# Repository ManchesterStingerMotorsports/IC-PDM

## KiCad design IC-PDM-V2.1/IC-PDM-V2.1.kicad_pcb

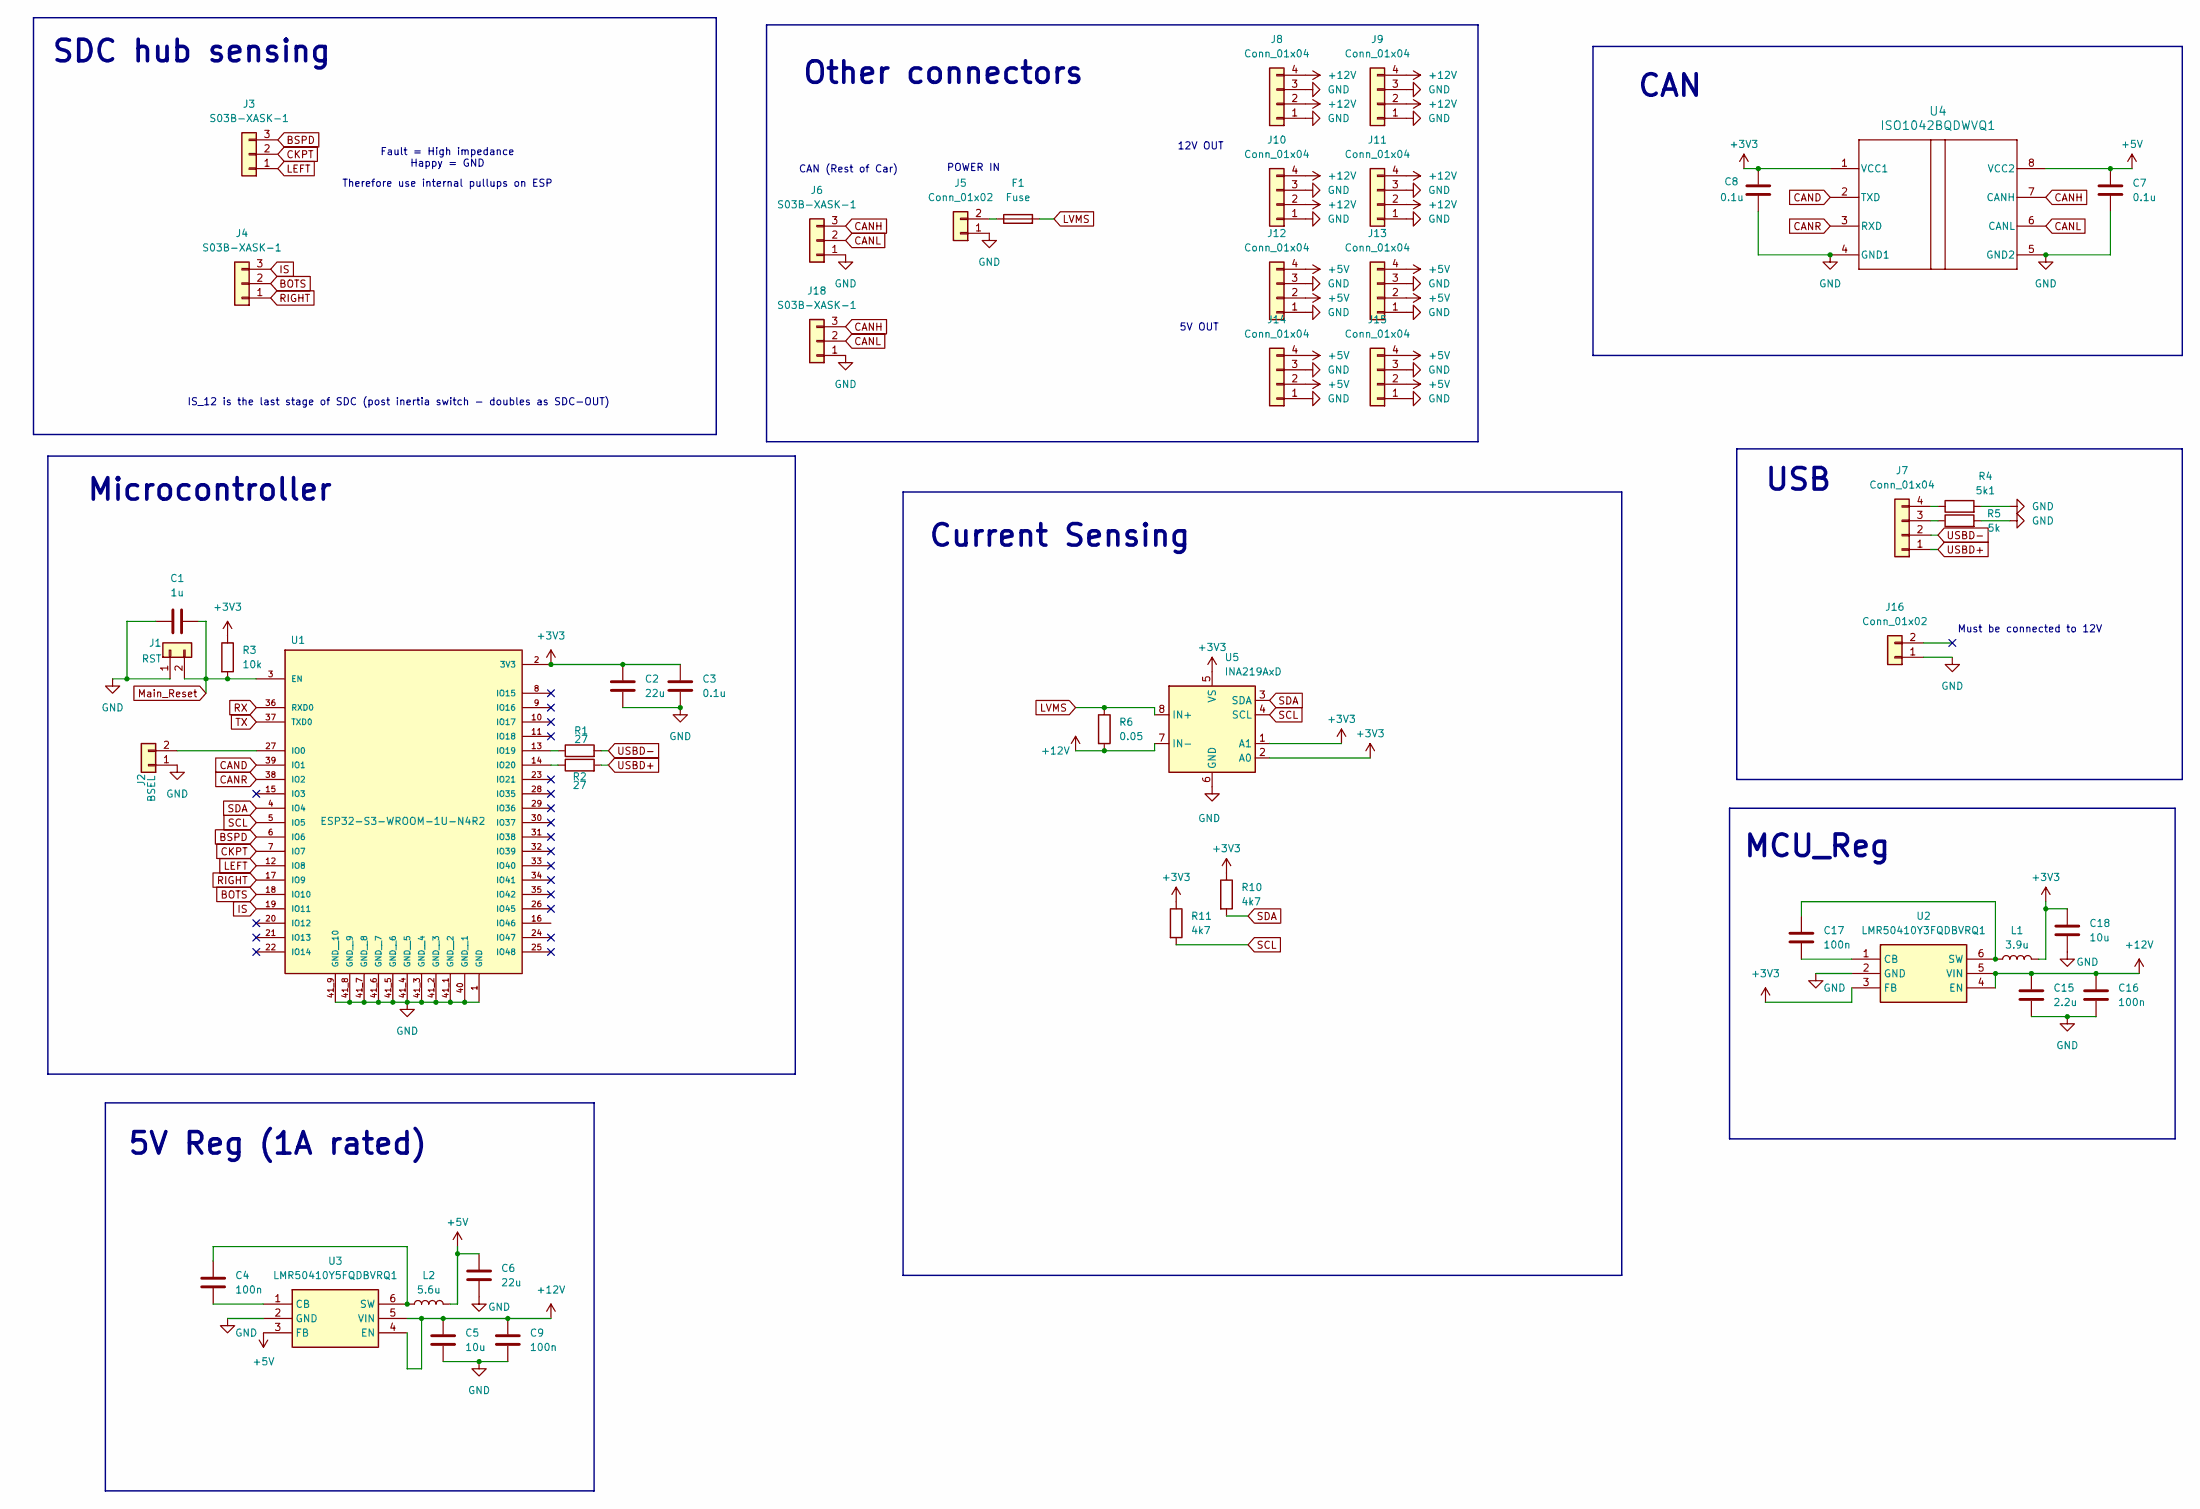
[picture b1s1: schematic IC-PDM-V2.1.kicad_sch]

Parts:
C1: 1u; C_0603_1608Metric
C2, C6: 22u; C_0603_1608Metric
C3, C7, C8: 0.1u; C_0603_1608Metric
C4, C9, C16, C17: 100n; C_0603_1608Metric
C5, C18: 10u; C_0603_1608Metric
C15: 2.2u; C_0603_1608Metric
F1: Fuse; FUSE_0PTF0078P_LTF
J1: RST; PinHeader_1x02_P2.54mm_Vertical
J2: BSEL; PinHeader_1x02_P2.54mm_Vertical
J3, J4, J6, J18: S03B-XASK-1; JST_XA_S03B-XASK-1_1x03_P2.50mm_Horizontal
J5, J16: Conn_01x02; JST_XA_S02B-XASK-1_1x02_P2.50mm_Horizontal
J7, J8, J9, J10, J11, J12, J13, J14, J15: Conn_01x04; JST_XA_S04B-XASK-1_1x04_P2.50mm_Horizontal
L1: 3.9u; WE-TPC_4828
L2: 5.6u; WE-TPC_4828
R1, R2: 27; R_0603_1608Metric
R3: 10k; R_0603_1608Metric
R4: 5k1; R_0603_1608Metric
R5: 5k; R_0603_1608Metric
R6: 0.05; R_2512_6332Metric
R10, R11: 4k7; R_0603_1608Metric
U1: ESP32-S3-WROOM-1U-N4R2; ESP32-S3-WROOM-1U; PARTREV v1.1
U2: LMR50410Y3FQDBVRQ1; Regulator_Switching_SOT-23-6; Mouser Part Number 595-R50410Y3FQDBVRQ1
U3: LMR50410Y5FQDBVRQ1; Regulator_Switching_SOT-23-6; Mouser Part Number 595-R50410Y3FQDBVRQ1
U4: ISO1042BQDWVQ1; DWV0008A-MFG
U5: INA219AxD; SOIC-8_3.9x4.9mm_P1.27mm

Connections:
+3V3: C2.2, C3.2, C8.2, C18.1, L1.2, R3.1, R10.1, R11.1, U1.2 (3V3), U2.3 (FB), U4.1 (VCC1), U5.1 (A1), U5.2 (A0), U5.5 (VS)
+5V: C6.1, C7.2, J12.2, J12.4, J13.2, J13.4, J14.2, J14.4, J15.2, J15.4, L2.2, U3.3 (FB), U4.8 (VCC2)
+12V: C5.1, C9.1, C15.1, C16.1, J8.2, J8.4, J9.2, J9.4, J10.2, J10.4, J11.2, J11.4, R6.2, U2.4 (EN), U2.5 (VIN), U3.4 (EN), U3.5 (VIN), U5.7 (IN-)
BOTS: J4.2, U1.18 (IO10)
BSPD: J3.3, U1.6 (IO6)
CAND: U1.39 (IO1), U4.2 (TXD)
CANH: J6.3, J18.3, U4.7 (CANH)
CANL: J6.2, J18.2, U4.6 (CANL)
CANR: U1.38 (IO2), U4.3 (RXD)
CKPT: J3.2, U1.7 (IO7)
GND: C1.1, C2.1, C3.1, C5.2, C6.2, C7.1, C8.1, C9.2, C15.2, C16.2, C18.2, J1.1, J2.1, J5.1, J6.1, J8.1, J8.3, J9.1, J9.3, J10.1, J10.3, J11.1, J11.3, J12.1, J12.3, J13.1, J13.3, J14.1, J14.3, J15.1, J15.3, J16.1 (Pin_1_1), J18.1, R4.2, R5.2, U1.1 (GND), U1.40 (GND__1), U1.41_1 (GND__2), U1.41_2 (GND__3), U1.41_3 (GND__4), U1.41_4 (GND__5), U1.41_5 (GND__6), U1.41_6 (GND__7), U1.41_7 (GND__8), U1.41_8 (GND__9), U1.41_9 (GND__10), U2.2 (GND), U3.2 (GND), U4.4 (GND1), U4.5 (GND2), U5.6 (GND)
IS: J4.3, U1.19 (IO11)
LEFT: J3.1, U1.12 (IO8)
LVMS: F1.2, R6.1, U5.8 (IN+)
Main_Reset: C1.2, J1.2, R3.2, U1.3 (EN)
unnamed: J2.2, U1.27 (IO0)
unnamed: F1.1, J5.2
unnamed: J7.3, R5.1
unnamed: J7.4, R4.1
unnamed: R1.1, U1.13 (IO19)
unnamed: R2.1, U1.14 (IO20)
unnamed: C17.2, U2.1 (CB)
unnamed: C17.1, L1.1, U2.6 (SW)
unnamed: C4.2, U3.1 (CB)
unnamed: C4.1, L2.1, U3.6 (SW)
RIGHT: J4.1, U1.17 (IO9)
RX: U1.36 (RXD0)
SCL: R11.2, U1.5 (IO5), U5.4 (SCL)
SDA: R10.2, U1.4 (IO4), U5.3 (SDA)
TX: U1.37 (TXD0)
USBD+: J7.1, R2.2
USBD-: J7.2, R1.2

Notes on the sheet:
POWER IN
Therefore use internal pullups on ESP
SDC hub sensing
Other connectors
5V OUT
CAN
USB
IS_12 is the last stage of SDC (post inertia switch - doubles as SDC-OUT)
(1A rated)
Must be connected to 12V
CAN (Rest of Car)
MCU_Reg
Microcontroller
Fault = High impedance Happy = GND
5V Reg
12V OUT
Current Sensing

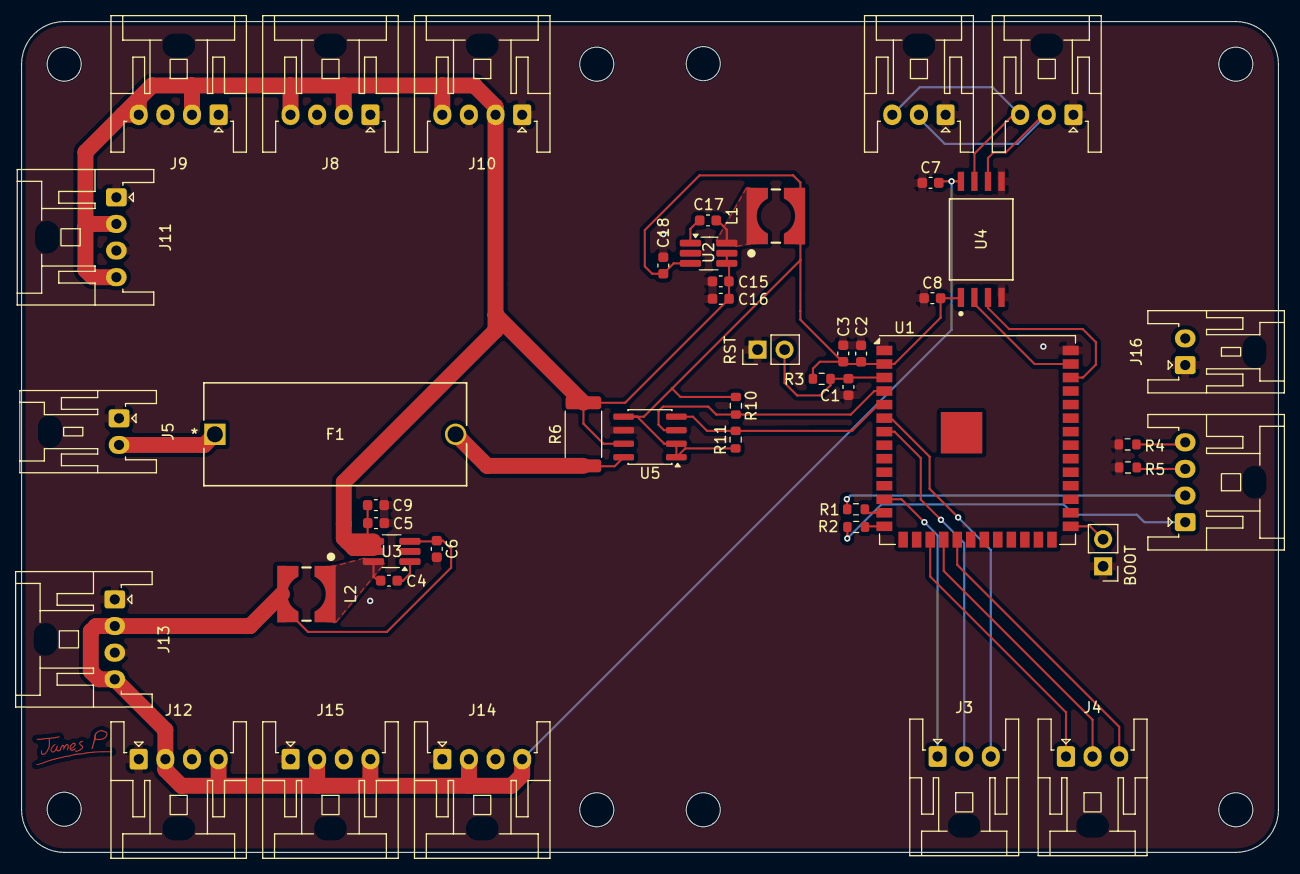
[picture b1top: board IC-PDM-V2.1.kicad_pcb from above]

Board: 2 copper layers, 118.0 x 78.0 mm, 46 parts (0 on the bottom side), 30 nets.

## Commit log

2026-02-05 First Commit
    Fixed Board layout & schem has passed design review.
    Routing needs to happen
2026-02-09 Bosh
    Routed PCB and fixed schematic
2026-02-09 Bosh v2
    Reuploaded updated schematic PDF
2026-06-09 Ready to order
